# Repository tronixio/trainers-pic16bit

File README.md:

# PIC 16-Bit Trainers Boards.

## Schematics.

- [**Nano** Trainer.](https://github.com/tronixio/trainers-pic16bit/blob/main/Kicad/nano/extras/schematic.pdf)
- [TODO - Micro Trainer.](https://github.com/tronixio/trainers-pic8bit/blob/main/Kicad/micro/extras/schematic.pdf)
- [**Mini** Trainer.](https://github.com/tronixio/trainers-pic16bit/blob/main/Kicad/mini/extras/schematic.pdf)
- [**PIC 16-Bit** Trainer.](https://github.com/tronixio/trainers-pic16bit/blob/main/Kicad/trainer/extras/schematic.pdf)

## Firmwares.

- [TODO]()

## Hats & Modules.

- [Trainer Hats](https://github.com/tronixio/modules)
- [Trainer Modules (GPIO/UART/I2C/SPI)](https://github.com/tronixio/modules)

### MINI Trainer.

- [PIC24FJxxGA002 - XC16 - LCD - ADC - SWITCHS - ROTARY ENCODER.](https://github.com/tronixio/trainers-pic16bit/blob/main/Firmwares/pic24fjxxga/pic24fjxxga002-mini-xc16-lcd.md)
- [PIC24FJxxGA002 - XC16 - EUSART - ADC - SWITCHS - ROTARY ENCODER.](https://github.com/tronixio/trainers-pic16bit/blob/main/Firmwares/pic24fjxxga/pic24fjxxga002-mini-xc16-eusart.md)
- [PIC24FJxxGA102 - XC16 - LCD - ADC - SWITCHS - ROTARY ENCODER.](https://github.com/tronixio/trainers-pic16bit/blob/main/Firmwares/pic24fjxxga/pic24fjxxga102-mini-xc16-lcd.md)
- [PIC24FJxxGA102 - XC16 - EUSART - ADC - SWITCHS - ROTARY ENCODER.](https://github.com/tronixio/trainers-pic16bit/blob/main/Firmwares/pic24fjxxga/pic24fjxxga102-mini-xc16-eusart.md)

## NANO Trainer Top.

## NANO Trainer Bottom.

## MINI Trainer Top.

## MINI Trainer Bottom.

## PIC 16-Bit Trainer Top.

## PIC 16-Bit Trainer Bottom.

## Note.

- DRAFT : Prototype OK, last check schematic, PCB & code can be modify.
- TODO : Work in progress, prototype was not good, hardware, PCB and code can be rework.

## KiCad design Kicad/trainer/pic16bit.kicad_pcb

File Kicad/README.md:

# Trainers Boards PIC 16-Bit.

- [Trainers Boards PIC 16-Bit.](https://github.com/tronixio/trainers-pic16bit#schematics)

## Notes.

- TODO : Work in progress, prototype was not good, hardware, PCB and code can be rework.
- DRAFT : Prototype OK, last check schematic, PCB & code can be modify.

## DISCLAIMER.

THIS CODE IS PROVIDED WITHOUT ANY WARRANTY OR GUARANTEES.
USERS MAY USE THIS CODE FOR DEVELOPMENT AND EXAMPLE PURPOSES ONLY.
AUTHORS ARE NOT RESPONSIBLE FOR ANY ERRORS, OMISSIONS, OR DAMAGES THAT COULD
RESULT FROM USING THIS FIRMWARE IN WHOLE OR IN PART.

---

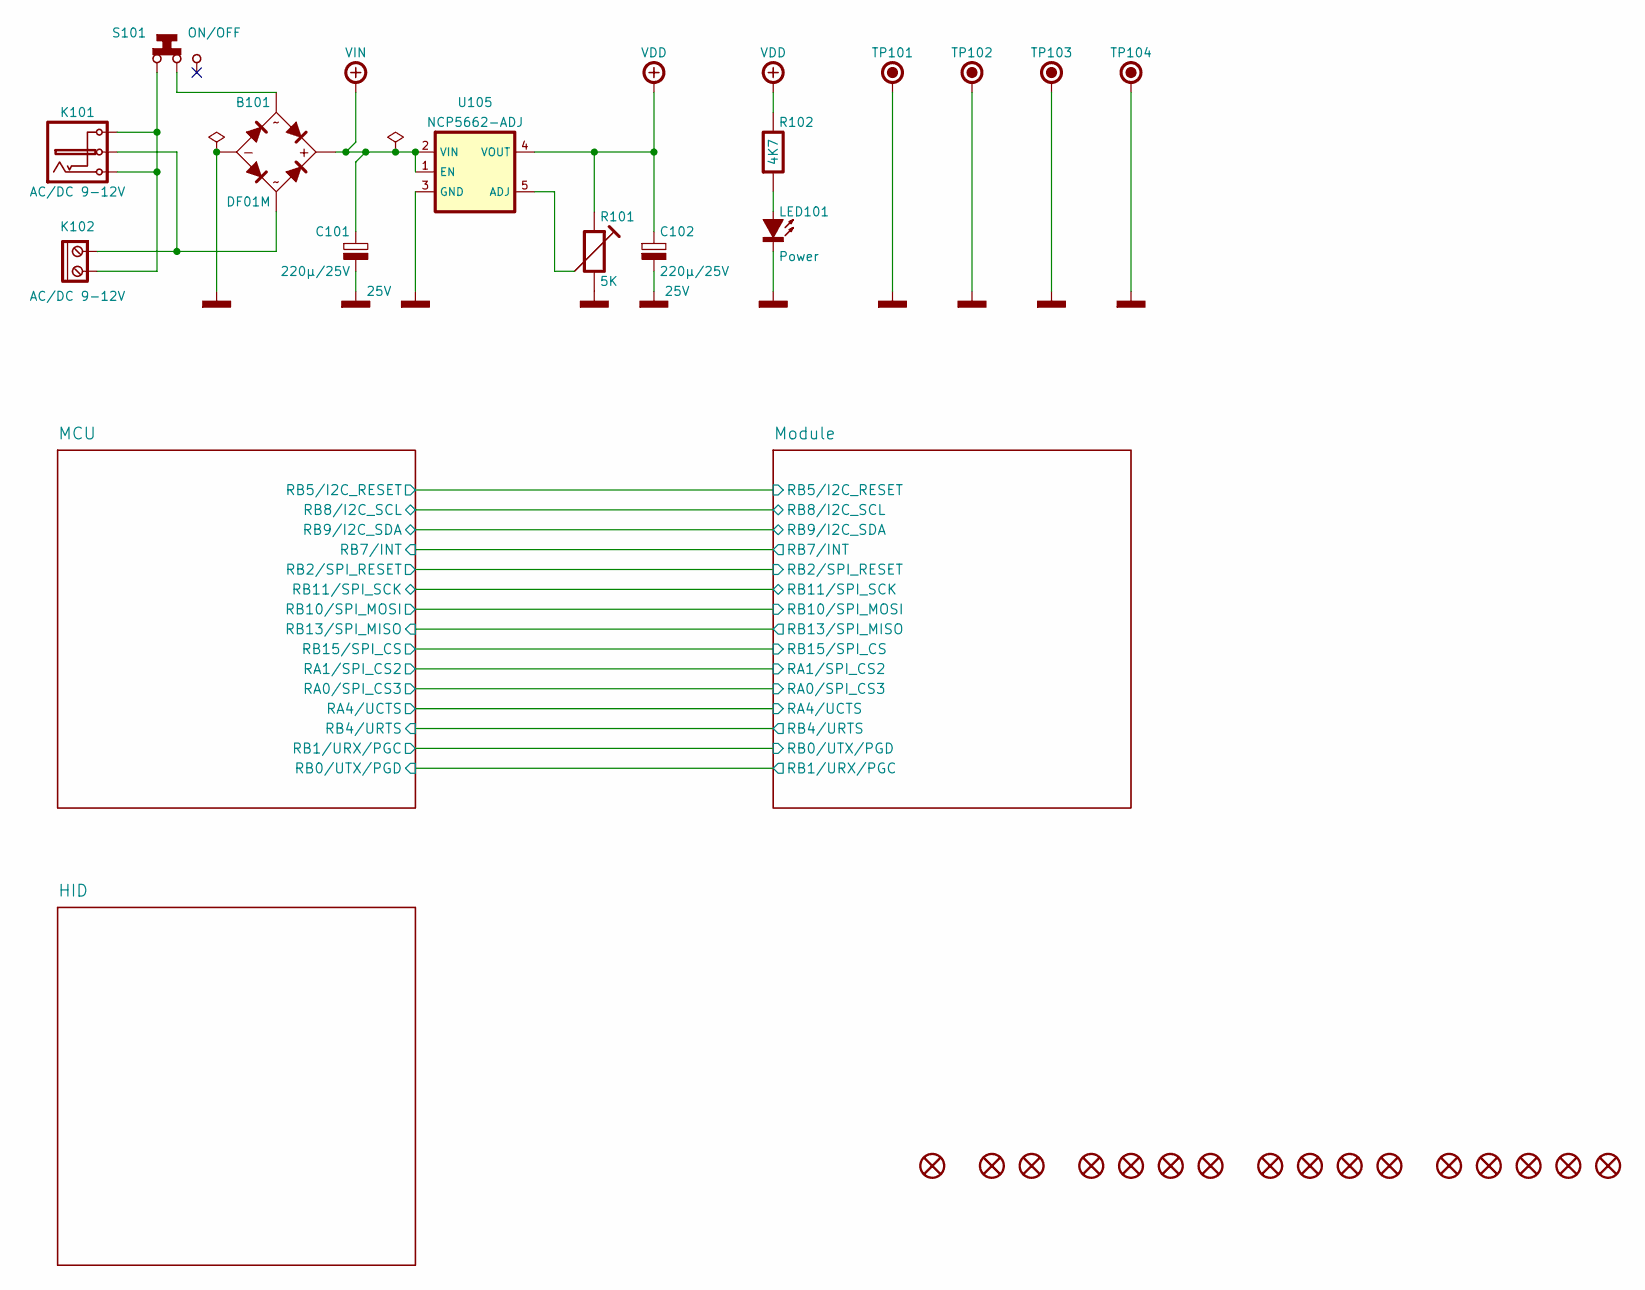
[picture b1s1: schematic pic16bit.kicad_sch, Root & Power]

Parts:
B101: DF01M; Mouser 512-DF01M
C101, C102: 220µ/25V; CAPACITOR-ELECTROLYTIC-RADIAL-080-115-035; Voltage 25V; Tolerance 20%; Mouser 647-UVZ1E221MPD
H101, H102, H103, H104: HARWIN-JUMPER-0254-14MM-BLACK; HARWIN-M20-7680-7683; Mouser 855-M7682
JP101: HARWIN-JUMPER-0254-06MM-BLACK; HARWIN-M20-7580-7583; Mouser 855-M7582
JP102: HARWIN-JUMPER-0254-06MM-RED; HARWIN-M20-7580-7583; Mouser 855-M7581
K101: AC/DC 9-12V; SAMESKY-PJ-102AH; Mouser 490-PJ-102AH
K102: AC/DC 9-12V; SAMESKY-TB006-508-02BE; Mouser 490-TB006-508-02BE
K103: PE-450-4X6X-BLACK; PE-450-4X6X; Mouser 450-476
LED101: Power; LED-TH-ROUND-05MM; Mouser 604-WP7113ID
R101: 5K; TRIMMER-64W; Tolerance 10%; Mouser 594-64W502
R102: 4K7; RESISTOR-TH-1016; Tolerance 5%; Mouser 594-SFR2500004701JR5
S101: ON/OFF; CK-1101M2; Mouser 611-1101M2S3CQE2
TP101, TP102, TP103: GND; KEYSTONE-5006; Mouser 534-5006
TP104: GND; KEYSTONE-2000-3; Mouser 534-2000-3
U101, U102, U103, U104: KEYSTONE-24283; Mouser 534-24283
U105: NCP5662-ADJ; TO-263-5-TABPIN3; Mouser 863-NCP5662DSADJR4G
X101, X102, X103, X104, X105: 3M-SJ5376; Mouser 517-SJ5376

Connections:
unnamed: B101.3, K101.1, K102.1
unnamed: B101.4, S101.2
unnamed: K101.2, K101.3, K102.2, S101.1
unnamed: LED101.2 (A), R102.2
unnamed: R101.2, U105.5 (ADJ)
POWER-GND: B101.2, C101.2, C102.2, LED101.1 (C), R101.1, TP101.1, TP102.1, TP103.1, TP104.1, U105.3 (GND); also elsewhere on the board
POWER-VDD: C102.1, R101.3, R102.1, U105.4 (VOUT); also elsewhere on the board
POWER-VIN: B101.1, C101.1, U105.1 (EN), U105.2 (VIN); also elsewhere on the board

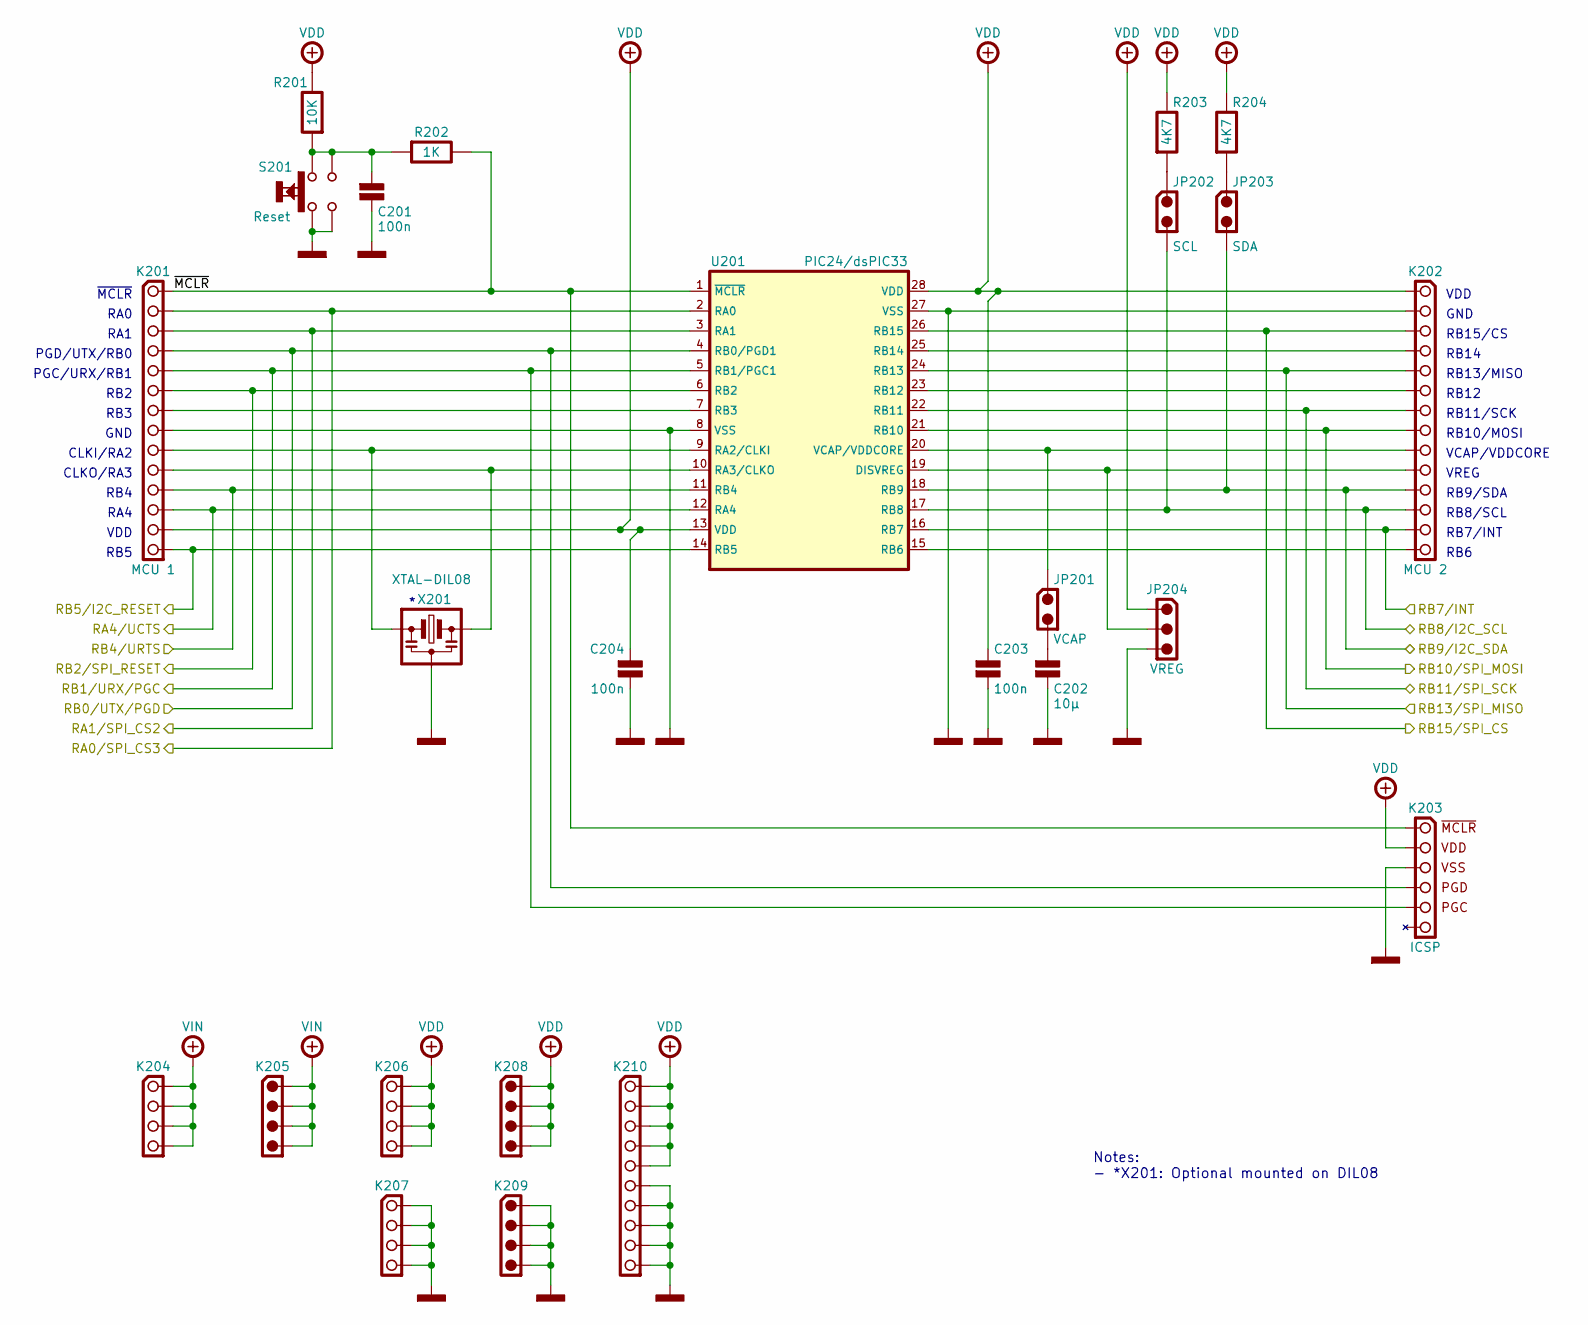
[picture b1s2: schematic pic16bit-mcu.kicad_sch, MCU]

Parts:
C201, C203, C204: 100n; KEMET-C315; Tolerance 20%; Voltage 50V; Mouser 80-C315C104M5U
C202: 10µ; KEMET-C322; Tolerance 10%; Voltage 25V; Mouser 80-C322C106K3R
JP201: VCAP; HARWIN-M20-975024x; Mouser 855-M20-975024
JP202: SCL; HARWIN-M20-999024x; Mouser 855-M20-999024
JP203: SDA; HARWIN-M20-999024x; Mouser 855-M20-999024
JP204: VREG; HARWIN-M20-975034x; Mouser 855-M20-975034
K201: MCU 1; HARWIN-M20-782144x; Mouser 855-M20-782144
K202: MCU 2; HARWIN-M20-782144x; Mouser 855-M20-782144
K203: ICSP; SAMTEC-SSW-106-02-T-S-RA; Mouser 200-SSW10602TSRA
K204: VIN; HARWIN-M20-782044x; Mouser 855-M20-782044
K205: VIN; HARWIN-M20-999044x; Mouser 855-M20-999044
K206: VDD; HARWIN-M20-782044x; Mouser 855-M20-782044
K207: GND; HARWIN-M20-782044x; Mouser 855-M20-782044
K208: VDD; HARWIN-M20-999044x; Mouser 855-M20-999044
K209: GND; HARWIN-M20-999044x; Mouser 855-M20-999044
K210: VDD & GND; HARWIN-M20-782104x; Mouser 855-M20-782104
R201: 10K; RESISTOR-TH-1016; Tolerance 5%; Mouser 594-SFR2500001002JA5
R202: 1K; RESISTOR-TH-1016; Tolerance 5%; Mouser 594-SFR2500001001JR5
R203, R204: 4K7; RESISTOR-TH-1016; Tolerance 5%; Mouser 594-SFR2500004701JR5
S201: Reset; CK-KSA-TH; Mouser 611-KSA0M911LFT
U201: PIC24/dsPIC33; DIP-28-W762
X201: XTAL-DIL08; DIP-08-W762-SOCKET; Mouser 575-144308

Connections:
/MCU/RA0/SPI_CS3: K201.2, U201.2 (RA0); also elsewhere on the board
/MCU/RA1/SPI_CS2: K201.3, U201.3 (RA1); also elsewhere on the board
/MCU/RA4/UCTS: K201.12, U201.12 (RA4); also elsewhere on the board
/MCU/RB0/UTX/PGD: K201.4, K203.3 (PGD), U201.4 (RB0/PGD1); also elsewhere on the board
/MCU/RB1/URX/PGC: K201.5, K203.2 (PGC), U201.5 (RB1/PGC1); also elsewhere on the board
/MCU/RB2/SPI_RESET: K201.6, U201.6 (RB2); also elsewhere on the board
/MCU/RB4/URTS: K201.11, U201.11 (RB4); also elsewhere on the board
/MCU/RB5/I2C_RESET: K201.14, U201.14 (RB5); also elsewhere on the board
/MCU/RB7/INT: K202.13, U201.16 (RB7); also elsewhere on the board
/MCU/RB8/I2C_SCL: JP202.2, K202.12, U201.17 (RB8); also elsewhere on the board
/MCU/RB9/I2C_SDA: JP203.2, K202.11, U201.18 (RB9); also elsewhere on the board
/MCU/RB10/SPI_MOSI: K202.8, U201.21 (RB10); also elsewhere on the board
/MCU/RB11/SPI_SCK: K202.7, U201.22 (RB11); also elsewhere on the board
/MCU/RB13/SPI_MISO: K202.5, U201.24 (RB13); also elsewhere on the board
/MCU/RB15/SPI_CS: K202.3, U201.26 (RB15); also elsewhere on the board
/MCU/~MCLR: K201.1, K203.6 (~MCLR), R202.1, U201.1 (~MCLR)
unnamed: C201.1, R201.2, R202.2, S201.1, S201.2
unnamed: C202.1, JP201.2
unnamed: JP202.1, R203.2
unnamed: JP203.1, R204.2
unnamed: K201.7, U201.7 (RB3)
unnamed: K201.9, U201.9 (RA2/CLKI), X201.3, X201.4
unnamed: K201.10, U201.10 (RA3/CLKO), X201.5, X201.6
unnamed: K202.4, U201.25 (RB14)
unnamed: K202.6, U201.23 (RB12)
unnamed: JP201.1, K202.9, U201.20 (VCAP/VDDCORE)
unnamed: JP204.2, K202.10, U201.19 (DISVREG)
unnamed: K202.14, U201.15 (RB6)
POWER-GND: C201.2, C202.2, C203.2, C204.2, JP204.3, K201.8, K202.2, K203.4 (GND), K207.1, K207.2, K207.3, K207.4, K209.1, K209.2, K209.3, K209.4, K210.6, K210.7, K210.8, K210.9, K210.10, S201.3, S201.4, U201.8 (VSS), U201.27 (VSS), X201.1, X201.2, X201.7, X201.8; also elsewhere on the board
POWER-VDD: C203.1, C204.1, JP204.1, K201.13, K202.1, K203.5 (VCC), K206.1, K206.2, K206.3, K206.4, K208.1, K208.2, K208.3, K208.4, K210.1, K210.2, K210.3, K210.4, K210.5, R201.1, R203.1, R204.1, U201.13 (VDD), U201.28 (VDD); also elsewhere on the board
POWER-VIN: K204.1, K204.2, K204.3, K204.4, K205.1, K205.2, K205.3, K205.4; also elsewhere on the board

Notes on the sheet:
RB8/SCL
RB2
CLKI/RA2
VCAP/VDDCORE
PGC/URX/RB1
RA0
PGD/UTX/RB0
GND
RB15/CS
Notes: - *X201: Optional mounted on DIL08
VDD
~{MCLR}
CLKO/RA3
VREG
RB14
RB12
RA1
RB13/MISO
RB7/INT
RB3
RB10/MOSI
RB9/SDA
RB6
RA4
RB4
RB11/SCK
RB5

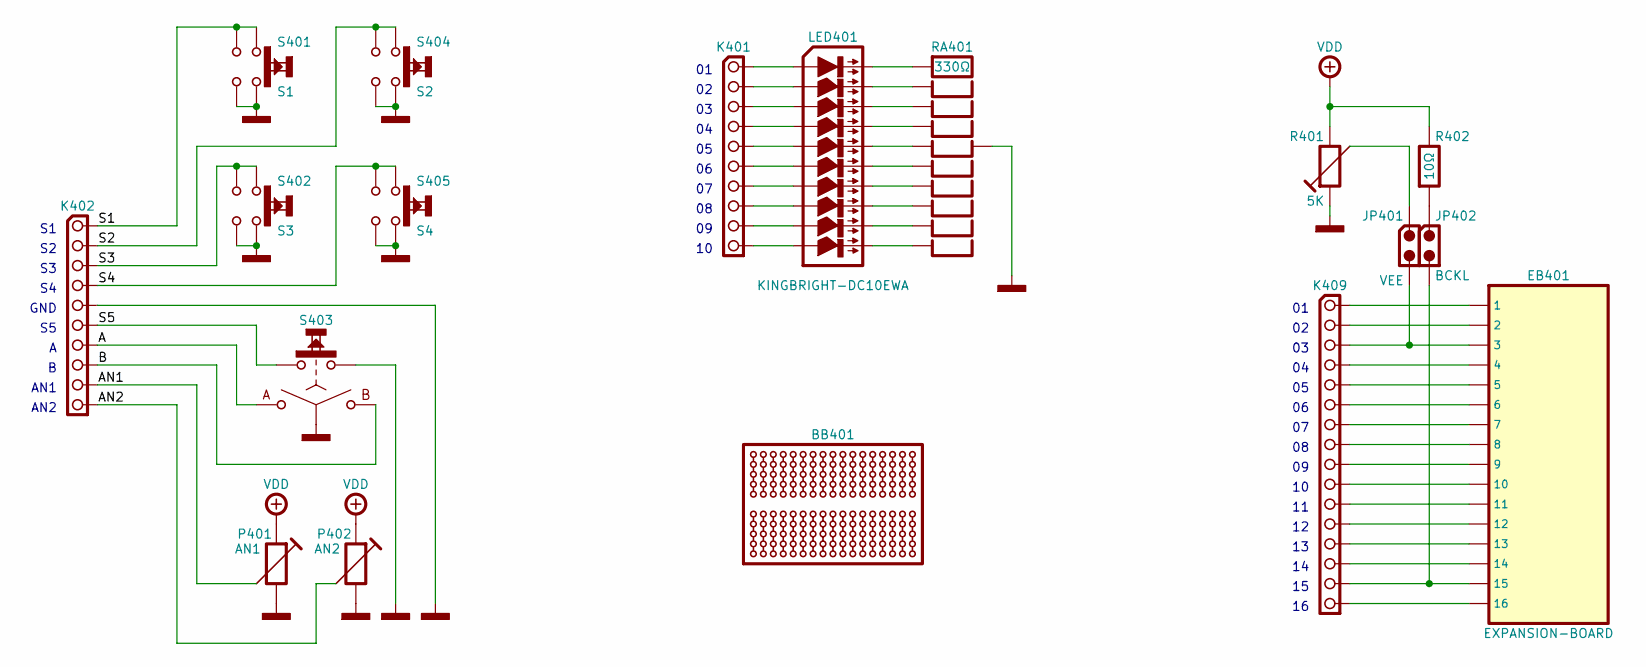
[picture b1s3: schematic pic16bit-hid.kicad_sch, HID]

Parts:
BB401: BREADBOARD-170; Mouser 854-BB170
EB401: EXPANSION-BOARD; TRONIXIO-EXPANSION-BOARD; Mouser 200-CES11601TS
JP401: VEE; HARWIN-M20-999024x; Mouser 855-M20-999024
JP402: BCKL; HARWIN-M20-999024x; Mouser 855-M20-999024
K401: LED ARRAY; HARWIN-M20-782104x; Mouser 855-M20-782104
K402: SWITCH, ENCODER & ANALOG; HARWIN-M20-782104x; Mouser 855-M20-782104
K409: EXPANSION BOARD; HARWIN-M20-782164x; Mouser 855-M20-782164
LED401: KINGBRIGHT-DC10EWA; KINGBRIGHT-DC; Mouser 604-DC-10EWA
P401: AN1; PIHER-PT10MV; Tolerance 20%; Mouser 531-PT10MV-10K
P402: AN2; PIHER-PT10MV; Tolerance 20%; Mouser 531-PT10MV-10K
R401: 5K; PIHER-PT10MV; Tolerance 20%; Mouser 531-PT10LV-5K
R402: 10Ω; RESISTOR-TH-1016; Tolerance 5%; Mouser 594-5043EM10R00J
RA401: 330Ω; BOURNS-4611X; Tolerance 2%; Mouser 652-4611X-1LF-330
S401: S1; CK-KSA-TH; Mouser 611-KSA0M911LFT
S402: S3; CK-KSA-TH; Mouser 611-KSA0M911LFT
S403: BOURNS-PEC12R-24DENTS; BOURNS-PEC12R-SWITCH; Mouser 652-PEC12R-4215F-S24
S404: S2; CK-KSA-TH; Mouser 611-KSA0M911LFT
S405: S4; CK-KSA-TH; Mouser 611-KSA0M911LFT

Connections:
/HID/A: K402.7, S403.1 (A)
/HID/AN1: K402.9, P401.2
/HID/AN2: K402.10, P402.2
/HID/B: K402.8, S403.3 (B)
/HID/S1: K402.1, S401.1, S401.2
/HID/S2: K402.2, S404.1, S404.2
/HID/S3: K402.3, S402.1, S402.2
/HID/S4: K402.4, S405.1, S405.2
/HID/S5: K402.6, S403.5
unnamed: JP401.1, R401.2
unnamed: JP402.1, R402.2
unnamed: K401.1, LED401.1 (A1)
unnamed: K401.2, LED401.2 (A2)
unnamed: K401.3, LED401.3 (A3)
unnamed: K401.4, LED401.4 (A4)
unnamed: K401.5, LED401.5 (A5)
unnamed: K401.6, LED401.6 (A6)
unnamed: K401.7, LED401.7 (A7)
unnamed: K401.8, LED401.8 (A8)
unnamed: K401.9, LED401.9 (A9)
unnamed: K401.10, LED401.10 (A10)
unnamed: EB401.1, K409.1
unnamed: EB401.2, K409.2
unnamed: EB401.3, JP401.2, K409.3
unnamed: EB401.4, K409.4
unnamed: EB401.5, K409.5
unnamed: EB401.6, K409.6
unnamed: EB401.7, K409.7
unnamed: EB401.8, K409.8
unnamed: EB401.9, K409.9
unnamed: EB401.10, K409.10
unnamed: EB401.11, K409.11
unnamed: EB401.12, K409.12
unnamed: EB401.13, K409.13
unnamed: EB401.14, K409.14
unnamed: EB401.15, JP402.2, K409.15
unnamed: EB401.16, K409.16
unnamed: LED401.20 (C1), RA401.2
unnamed: LED401.19 (C2), RA401.3
unnamed: LED401.18 (C3), RA401.4
unnamed: LED401.17 (C4), RA401.5
unnamed: LED401.16 (C5), RA401.6
unnamed: LED401.15 (C6), RA401.7
unnamed: LED401.14 (C7), RA401.8
unnamed: LED401.13 (C8), RA401.9
unnamed: LED401.12 (C9), RA401.10
unnamed: LED401.11 (C10), RA401.11
POWER-GND: K402.5, P401.1, P402.1, R401.3, RA401.1, S401.3, S401.4, S402.3, S402.4, S403.2 (C), S403.4, S404.3, S404.4, S405.3, S405.4; also elsewhere on the board
POWER-VDD: P401.3, P402.3, R401.1, R402.1; also elsewhere on the board

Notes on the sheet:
AN2
GND
AN1

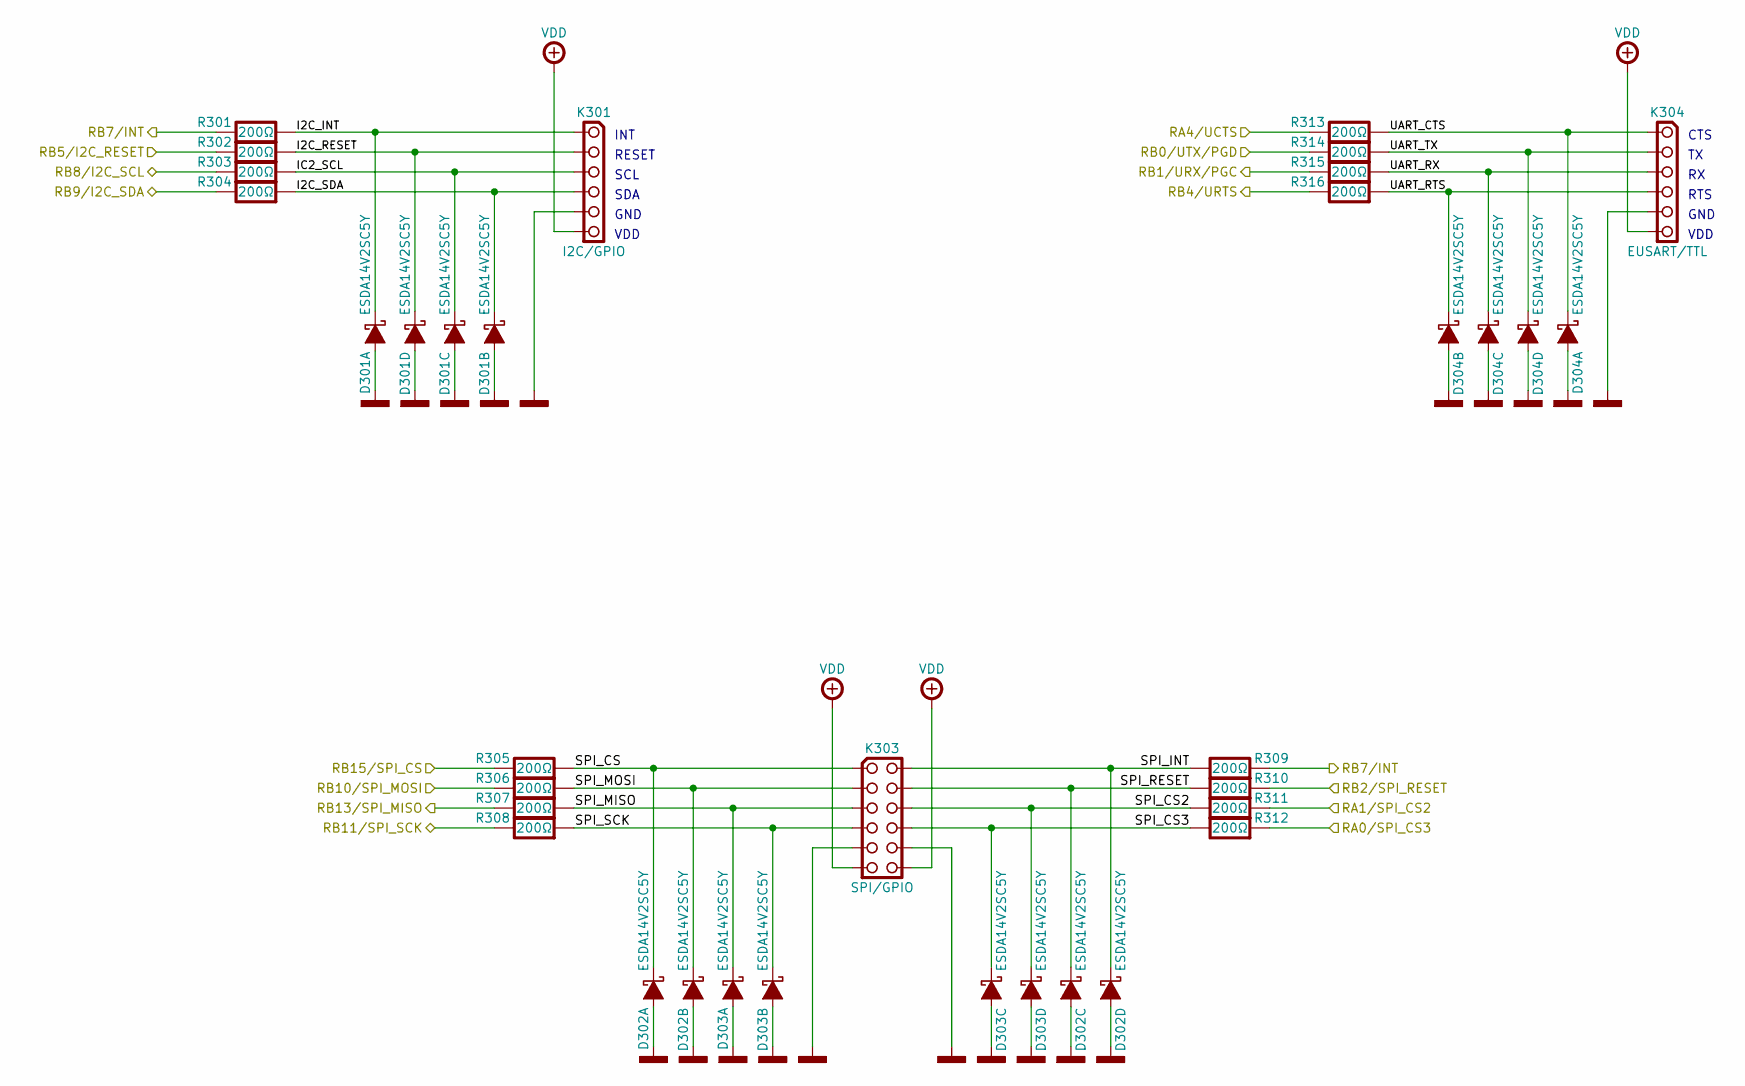
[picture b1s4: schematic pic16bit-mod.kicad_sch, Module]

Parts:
D301, D302, D303, D304: ESDA14V2SC5Y; SOT-23-5; Mouser 511-ESDA14V2SC5Y
K301: I2C/GPIO; SAMTEC-SSW-106-02-T-S-RA; Mouser 200-SSW10603TSRA
K303: SPI/GPIO; SAMTEC-SSW-106-02-T-D-RA; Mouser 200-SSW10602TDRA
K304: EUSART/TTL; SAMTEC-SSW-106-02-T-S-RA; Mouser 200-SSW10603TSRA
R301, R302, R303, R304, R305, R306, R307, R308, R309, R310, R311, R312, R313, R314, R315, R316: 200Ω; RESISTOR-SMD-1206; Tolerance 5%; Mouser 660-RK73B2BTTDD201J

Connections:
/MCU/RA0/SPI_CS3: R312.2; also elsewhere on the board
/MCU/RA1/SPI_CS2: R311.2; also elsewhere on the board
/MCU/RA4/UCTS: R313.1; also elsewhere on the board
/MCU/RB0/UTX/PGD: R315.1; also elsewhere on the board
/MCU/RB1/URX/PGC: R314.1; also elsewhere on the board
/MCU/RB2/SPI_RESET: R310.2; also elsewhere on the board
/MCU/RB4/URTS: R316.1; also elsewhere on the board
/MCU/RB5/I2C_RESET: R302.1; also elsewhere on the board
/MCU/RB7/INT: R301.1, R309.2; also elsewhere on the board
/MCU/RB8/I2C_SCL: R303.1; also elsewhere on the board
/MCU/RB9/I2C_SDA: R304.1; also elsewhere on the board
/MCU/RB10/SPI_MOSI: R306.1; also elsewhere on the board
/MCU/RB11/SPI_SCK: R308.1; also elsewhere on the board
/MCU/RB13/SPI_MISO: R307.1; also elsewhere on the board
/MCU/RB15/SPI_CS: R305.1; also elsewhere on the board
/Module/I2C_INT: D301.1 (C), K301.1, R301.2
/Module/I2C_RESET: D301.5 (C), K301.2, R302.2
/Module/I2C_SDA: D301.3 (C), K301.4, R304.2
/Module/IC2_SCL: D301.4 (C), K301.3, R303.2
/Module/SPI_CS: D302.1 (C), K303.1, R305.2
/Module/SPI_CS2: D303.5 (C), K303.6, R311.1
/Module/SPI_CS3: D303.4 (C), K303.8, R312.1
/Module/SPI_INT: D302.5 (C), K303.2, R309.1
/Module/SPI_MISO: D303.1 (C), K303.5, R307.2
/Module/SPI_MOSI: D302.3 (C), K303.3, R306.2
/Module/SPI_RESET: D302.4 (C), K303.4, R310.1
/Module/SPI_SCK: D303.3 (C), K303.7, R308.2
/Module/UART_CTS: D304.1 (C), K304.1, R313.2
/Module/UART_RTS: D304.3 (C), K304.4, R316.2
/Module/UART_RX: D304.4 (C), K304.3, R315.2
/Module/UART_TX: D304.5 (C), K304.2, R314.2
POWER-GND: D301.2 (A), D302.2 (A), D303.2 (A), D304.2 (A), K301.5, K303.9, K303.10, K304.5; also elsewhere on the board
POWER-VDD: K301.6, K303.11, K303.12, K304.6; also elsewhere on the board

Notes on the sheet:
INT
VDD
SCL
GND
SDA
CTS
RESET
RTS

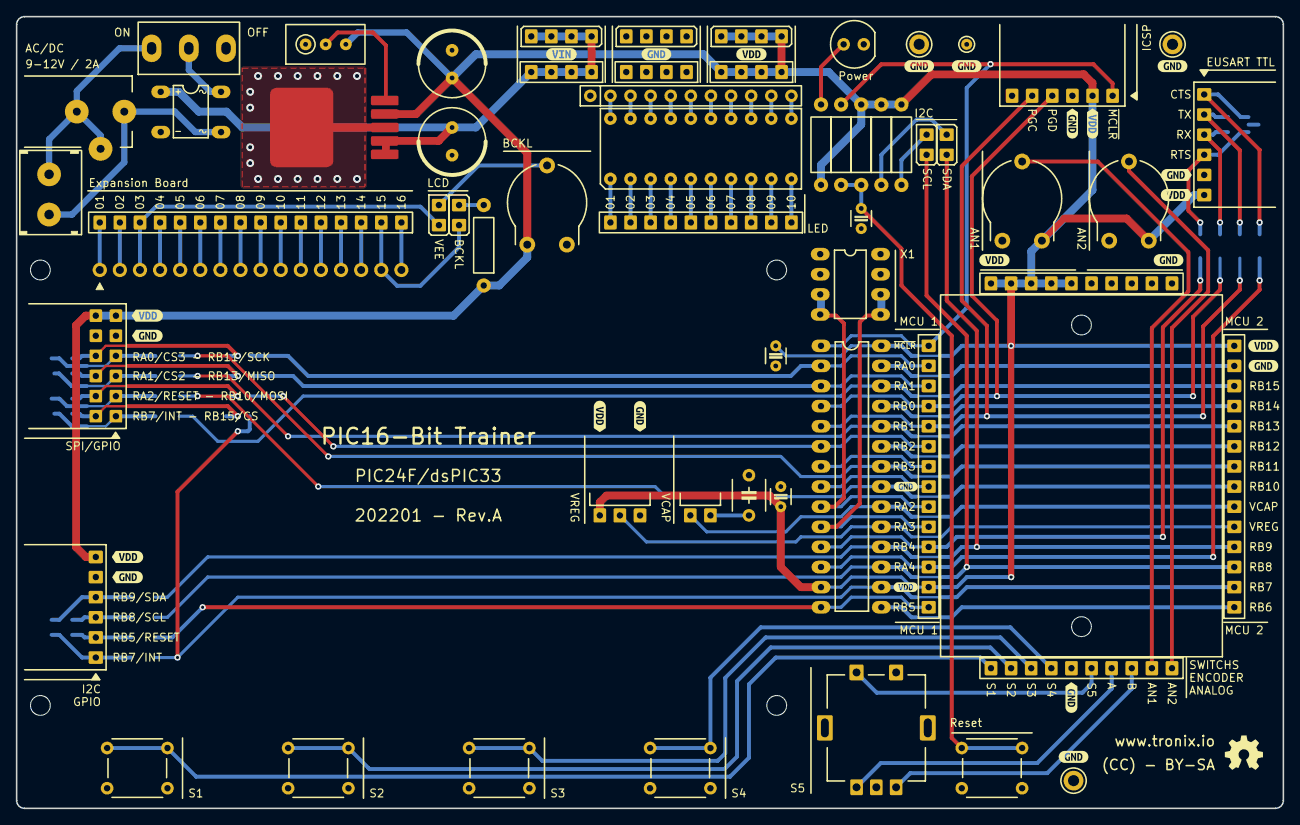
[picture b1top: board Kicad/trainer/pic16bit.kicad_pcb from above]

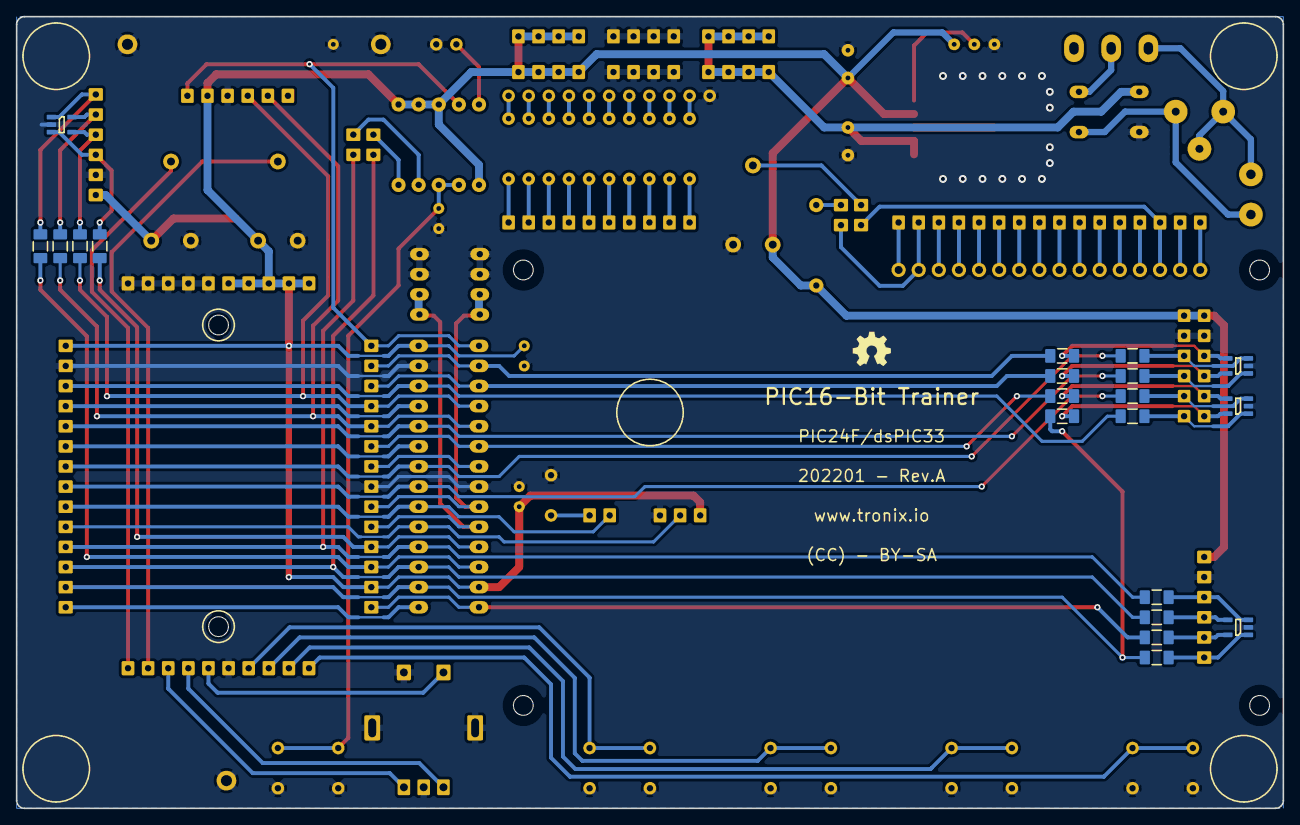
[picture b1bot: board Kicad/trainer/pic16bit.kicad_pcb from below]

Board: 2 copper layers, 160.0 x 100.0 mm, 120 parts (25 on the bottom side), 99 nets.

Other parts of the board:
kibuzzard-62A778D1: G***; kibuzzard-62A778D1
kibuzzard-62A778F0: G***; kibuzzard-62A778F0
kibuzzard-65F6F3D4: G***; kibuzzard-65F6F3D4
kibuzzard-65F6F3E0: G***; kibuzzard-65F6F3E0
kibuzzard-65F6F3EC: G***; kibuzzard-65F6F3EC
kibuzzard-65F6F3F9: G***; kibuzzard-65F6F3F9
kibuzzard-65F6F4AB: G***; kibuzzard-65F6F4AB
kibuzzard-65F6F4B8: G***; kibuzzard-65F6F4B8
kibuzzard-65F6F4C9: G***; kibuzzard-65F6F4C9
kibuzzard-65F6F4DA: G***; kibuzzard-65F6F4DA
kibuzzard-65F6F4F1: G***; kibuzzard-65F6F4F1
kibuzzard-65F6F42E: G***; kibuzzard-65F6F42E
kibuzzard-65F6F45D: G***; kibuzzard-65F6F45D
kibuzzard-65F6F46A: G***; kibuzzard-65F6F46A
kibuzzard-65F6F48D: G***; kibuzzard-65F6F48D
kibuzzard-65F6F405: G***; kibuzzard-65F6F405
kibuzzard-65F6F414: G***; kibuzzard-65F6F414
kibuzzard-65F6F420: G***; kibuzzard-65F6F420
kibuzzard-65F6F438: G***; kibuzzard-65F6F438
kibuzzard-65F6F442: G***; kibuzzard-65F6F442
kibuzzard-65F6F450: G***; kibuzzard-65F6F450
kibuzzard-65F6F480: G***; kibuzzard-65F6F480
kibuzzard-65F6F499: G***; kibuzzard-65F6F499
kibuzzard-65F6F500: G***; kibuzzard-65F6F500

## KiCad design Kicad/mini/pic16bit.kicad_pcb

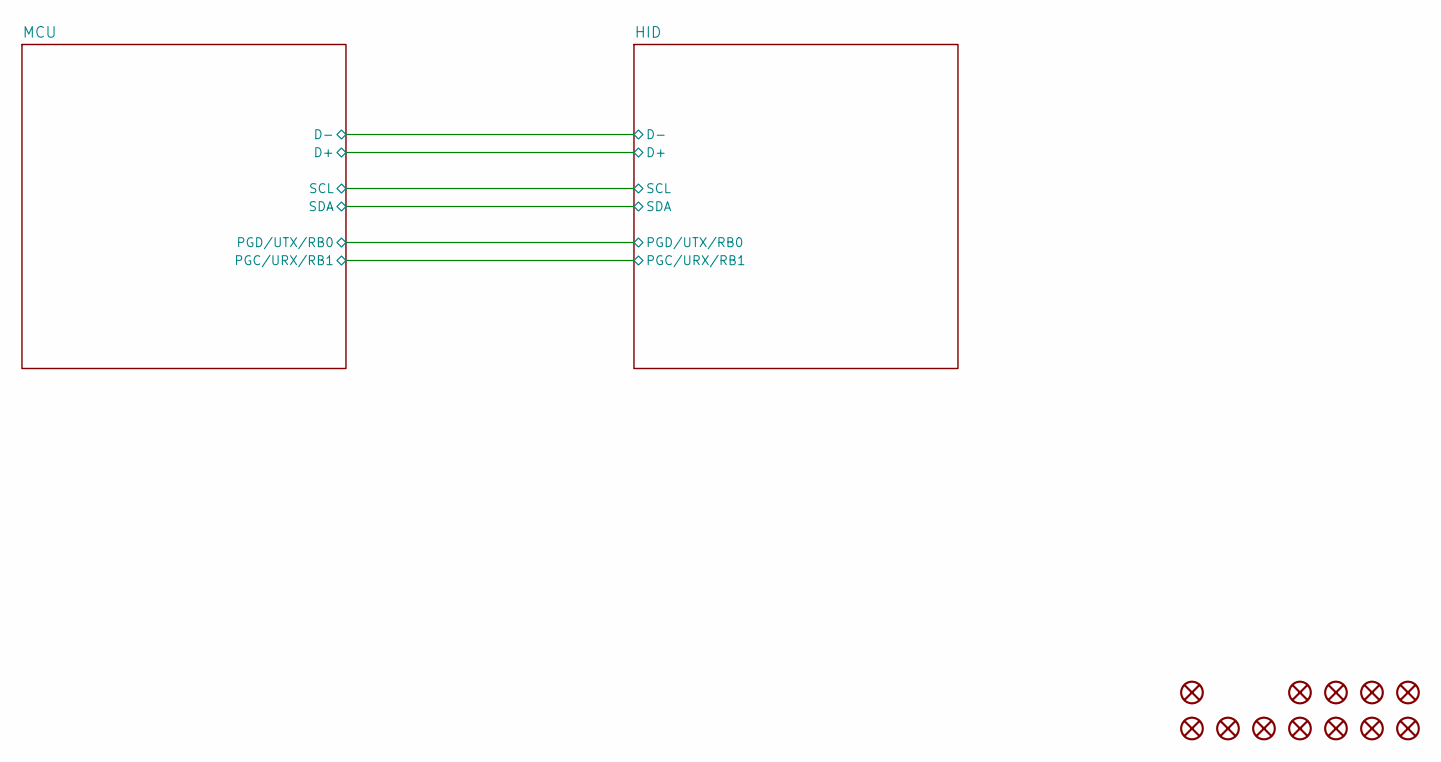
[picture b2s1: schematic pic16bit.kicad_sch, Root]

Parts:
H101, H102, H103, H104: KEYSTONE-9055; Mouser 534-9055
JP101, JP102, JP103, JP104, JP105, JP106, JP107: HARWIN-JUMPER-0254-06MM-BLACK; HARWIN-M20-7580-7583; Mouser 855-M7582
K101: PE-450-4X6X-BLACK; PE-450-4X6X; Mouser 450-476

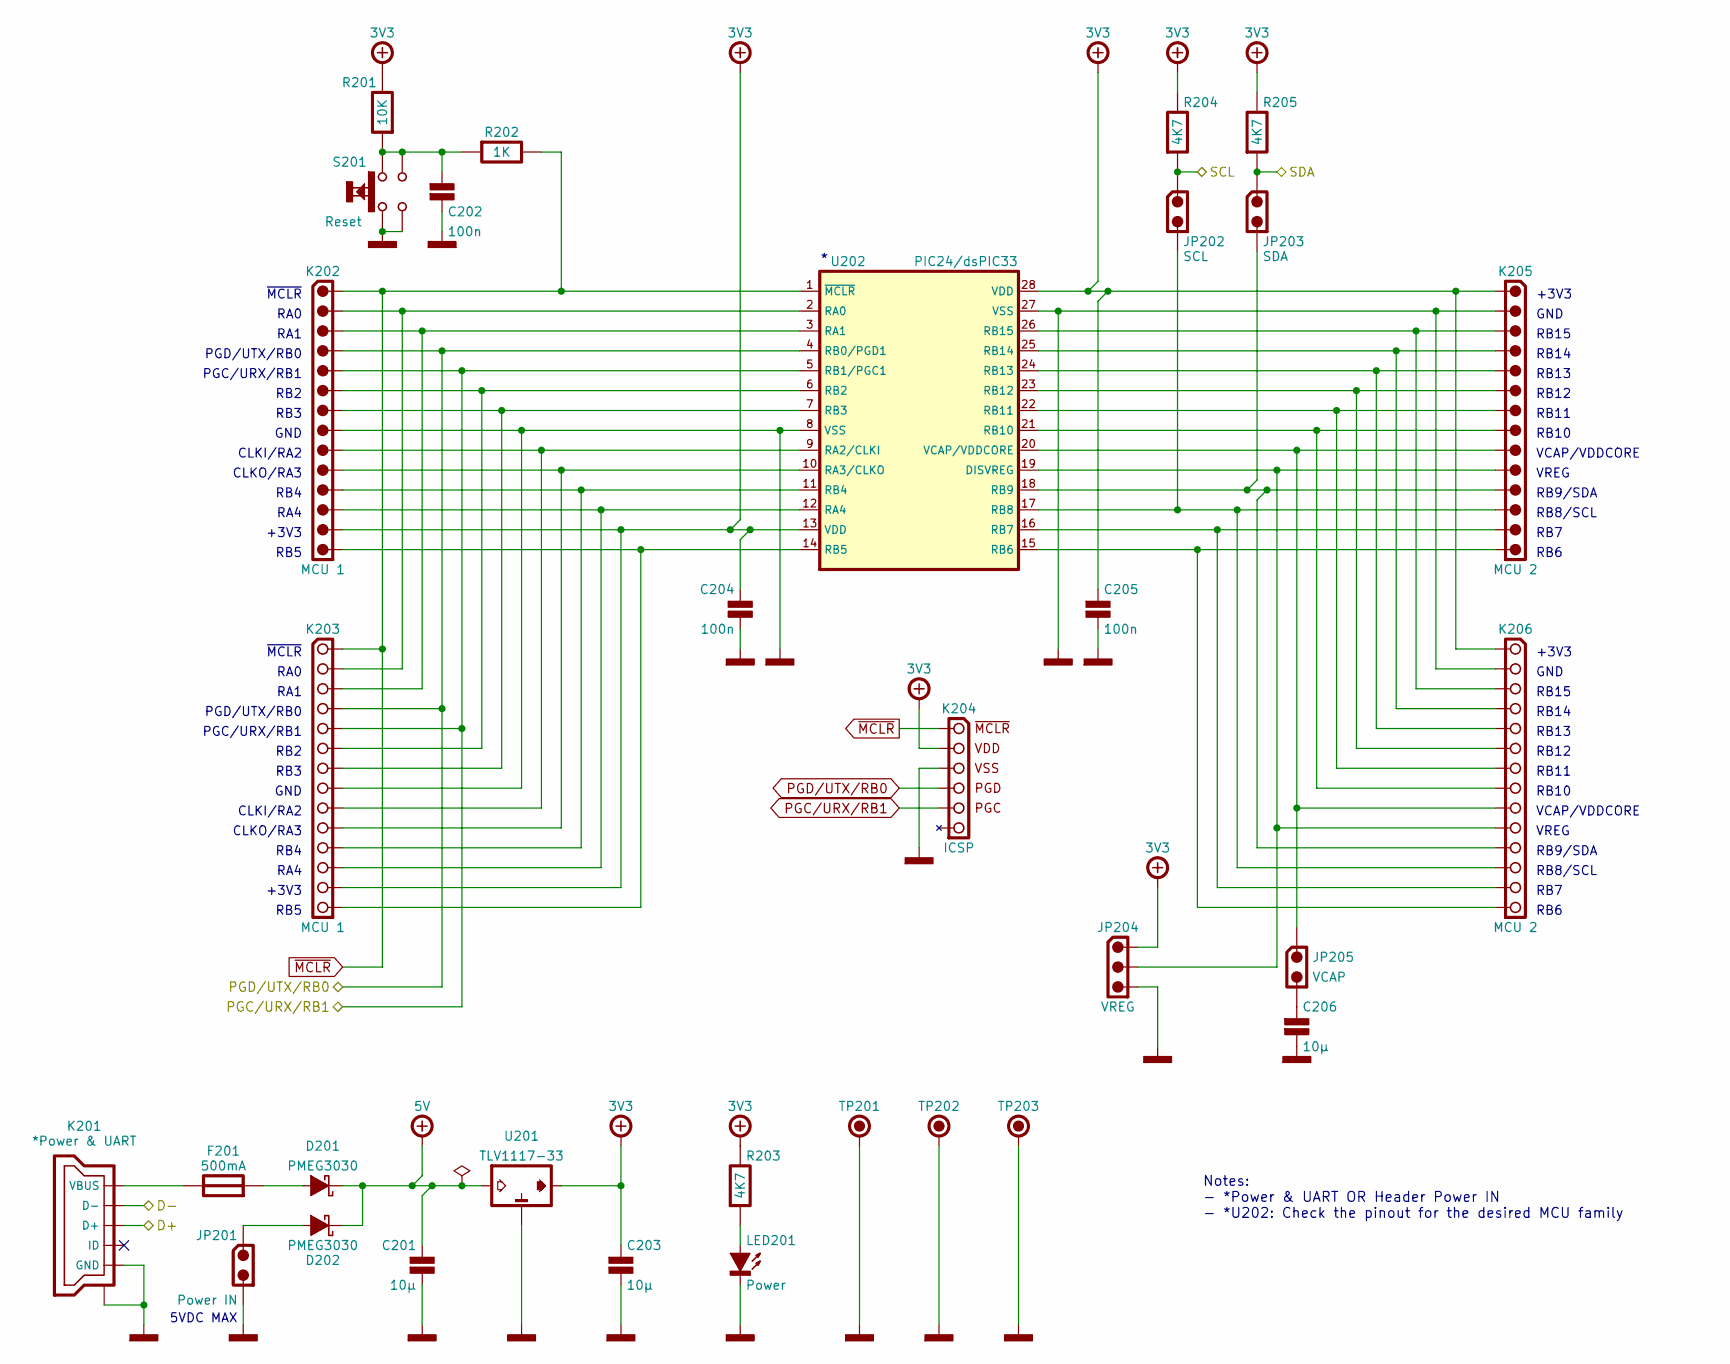
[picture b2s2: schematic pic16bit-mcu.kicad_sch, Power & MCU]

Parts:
C201, C203, C206: 10µ; CAPACITOR-SMD-1206; Voltage 25V; Tolerance 5%; Mouser 80-C1206C106J3R
C202, C204, C205: 100n; CAPACITOR-SMD-1206; Voltage 50V; Tolerance 5%; Mouser 80-C1206C104J5R
D201, D202: PMEG3030; SOD-128; Part Marking A5; Mouser 771-PMEG3030EP115
F201: 500mA; FUSE-SMD-1206; Mouser 652-MF-NSMF050-2
JP201: Power IN; HARWIN-M20-999024x; Mouser 855-M20-999024
JP202: SCL; HARWIN-M20-999024x; Mouser 855-M20-999024
JP203: SDA; HARWIN-M20-999024x; Mouser 855-M20-999024
JP204: VREG; HARWIN-M20-999034x; Mouser 855-M20-999034
JP205: VCAP; HARWIN-M20-999024x; Mouser 855-M20-999024
K201: *Power & UART; USB-TYPE-B-MICRO-TH; Mouser 649-10118193-0001LF
K202: MCU 1; HARWIN-M20-999144x; Mouser 855-M20-999144
K203: MCU 1; HARWIN-M20-782144x; Mouser 855-M20-782144
K204: ICSP; SAMTEC-SSW-106-02-T-S-RA; Mouser 200-SSW10602TSRA
K205: MCU 2; HARWIN-M20-999144x; Mouser 855-M20-999144
K206: MCU 2; HARWIN-M20-782144x; Mouser 855-M20-782144
LED201: Power; LED-SMD-1206; Mouser 604-APT3216LVBCD
R201: 10K; RESISTOR-SMD-1206; Tolerance 5%; Mouser 660-RK73B2BTTDD103J
R202: 1K; RESISTOR-SMD-1206; Tolerance 5%; Mouser 660-RK73B2BTTDD102J
R203, R204, R205: 4K7; RESISTOR-SMD-1206; Tolerance 5%; Mouser 660-RK73B2BTTDD472J
S201: Reset; ALPS-SKRPAC; Mouser 688-SKRPACE010
TP201, TP202: KEYSTONE-5006; Mouser 534-5006
TP203: KEYSTONE-2000-3; Mouser 534-2000-3
U201: TLV1117-33; SOT-223-3-TABPIN2; Mouser 595-TLV1117-33CDC
U202: PIC24/dsPIC33; DIP-28-W762; Mouser 579-P24FJ64GA102ISP

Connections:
/HID/D+: K201.3 (D+); also elsewhere on the board
/HID/D-: K201.2 (D-); also elsewhere on the board
/HID/SCL: JP202.1, R204.2; also elsewhere on the board
/HID/SDA: JP203.1, R205.2; also elsewhere on the board
unnamed: C202.1, R201.2, R202.2, S201.1, S201.2
unnamed: C206.1, JP205.2
unnamed: D201.2 (A), F201.2
unnamed: D202.2 (A), JP201.1
unnamed: F201.1, K201.1 (VBUS)
unnamed: K202.2, K203.2, U202.2 (RA0)
unnamed: K202.3, K203.3, U202.3 (RA1)
unnamed: K202.6, K203.6, U202.6 (RB2)
unnamed: K202.7, K203.7, U202.7 (RB3)
unnamed: K202.9, K203.9, U202.9 (RA2/CLKI)
unnamed: K202.10, K203.10, U202.10 (RA3/CLKO)
unnamed: K202.11, K203.11, U202.11 (RB4)
unnamed: K202.12, K203.12, U202.12 (RA4)
unnamed: K202.14, K203.14, U202.14 (RB5)
unnamed: K205.3, K206.3, U202.26 (RB15)
unnamed: K205.4, K206.4, U202.25 (RB14)
unnamed: K205.5, K206.5, U202.24 (RB13)
unnamed: K205.6, K206.6, U202.23 (RB12)
unnamed: K205.7, K206.7, U202.22 (RB11)
unnamed: K205.8, K206.8, U202.21 (RB10)
unnamed: JP205.1, K205.9, K206.9, U202.20 (VCAP/VDDCORE)
unnamed: JP204.2, K205.10, K206.10, U202.19 (DISVREG)
unnamed: JP203.2, K205.11, K206.11, U202.18 (RB9)
unnamed: JP202.2, K205.12, K206.12, U202.17 (RB8)
unnamed: K205.13, K206.13, U202.16 (RB7)
unnamed: K205.14, K206.14, U202.15 (RB6)
unnamed: LED201.2 (A), R203.2
PGC/URX/RB1: K202.5, K203.5, K204.2 (PGC), U202.5 (RB1/PGC1); also elsewhere on the board
PGD/UTX/RB0: K202.4, K203.4, K204.3 (PGD), U202.4 (RB0/PGD1); also elsewhere on the board
POWER-+3V3: C203.1, C204.1, C205.1, JP204.1, K202.13, K203.13, K204.5 (VCC), K205.1, K206.1, R201.1, R203.1, R204.1, R205.1, U201.2 (VOUT), U202.13 (VDD), U202.28 (VDD); also elsewhere on the board
POWER-+5V: C201.1, D201.1 (C), D202.1 (C), U201.3 (VIN); also elsewhere on the board
POWER-GND: C201.2, C202.2, C203.2, C204.2, C205.2, C206.2, JP201.2, JP204.3, K201.5 (GND), K201.SH (SHIELD), K202.8, K203.8, K204.4 (GND), K205.2, K206.2, LED201.1 (C), S201.3, S201.4, TP201.1, TP202.1, TP203.1, U201.1 (GND), U202.8 (VSS), U202.27 (VSS); also elsewhere on the board
~MCLR: K202.1, K203.1, K204.6 (~MCLR), R202.1, U202.1 (~MCLR)

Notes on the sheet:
RB8/SCL
RB2
Notes: - *Power & UART OR Header Power IN - *U202: Check the pinout for the desired MCU family
CLKI/RA2
RA1
RB11
VCAP/VDDCORE
RB13
RB6
VREG
PGC/URX/RB1
RA0
PGD/UTX/RB0
GND
RB12
RB15
+3V3
RB9/SDA
~{MCLR}
RB4
RB3
CLKO/RA3
RB10
RB14
RB7
RB5
RA4
5VDC MAX
